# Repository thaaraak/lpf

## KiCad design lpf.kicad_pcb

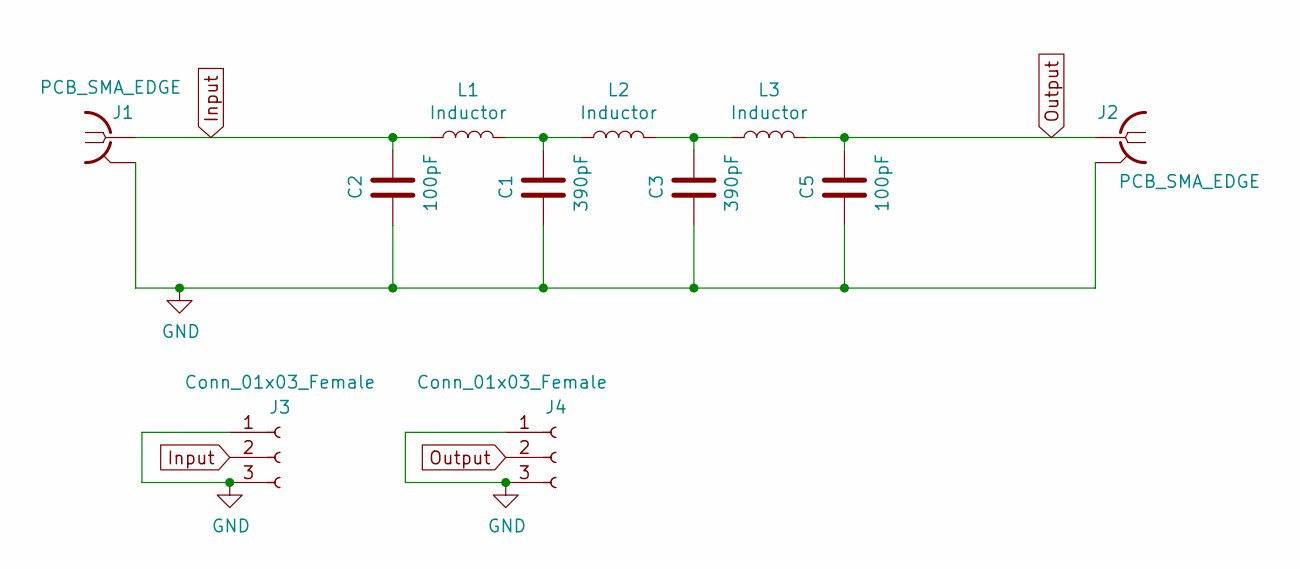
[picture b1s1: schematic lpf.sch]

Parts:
C1, C3: 390pF; Capacitor 1206
C2, C5: 100pF; Capacitor 1206
J1, J2: PCB_SMA_EDGE; PCB-SMA-EDGE
J3, J4: Conn_01x03_Female; PinHeader_1x03_P2.54mm_Vertical
L1, L2, L3: Inductor; T37_Inductor

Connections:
GND: C1.1, C2.1, C3.1, C5.1, J1.2, J2.2, J3.1, J3.3, J4.1, J4.3
Input: C2.2, J1.1, J3.2, L1.1
unnamed: C1.2, L1.2, L2.1
unnamed: C3.2, L2.2, L3.1
Output: C5.2, J2.1, J4.2, L3.2

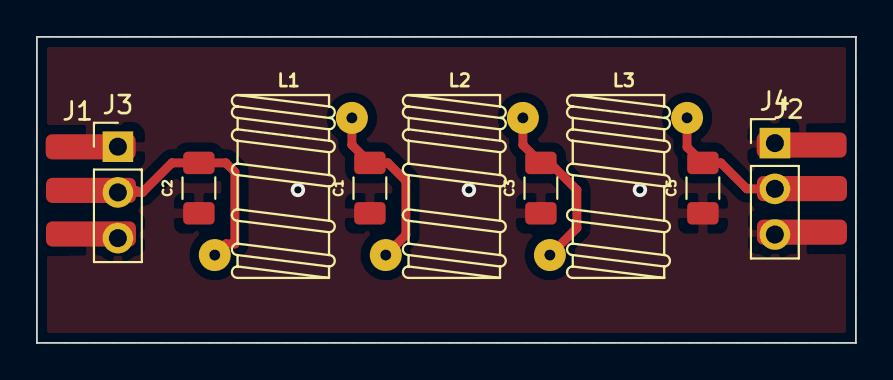
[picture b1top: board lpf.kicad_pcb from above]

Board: 2 copper layers, 45.5 x 17.0 mm, 11 parts (0 on the bottom side), 5 nets.
